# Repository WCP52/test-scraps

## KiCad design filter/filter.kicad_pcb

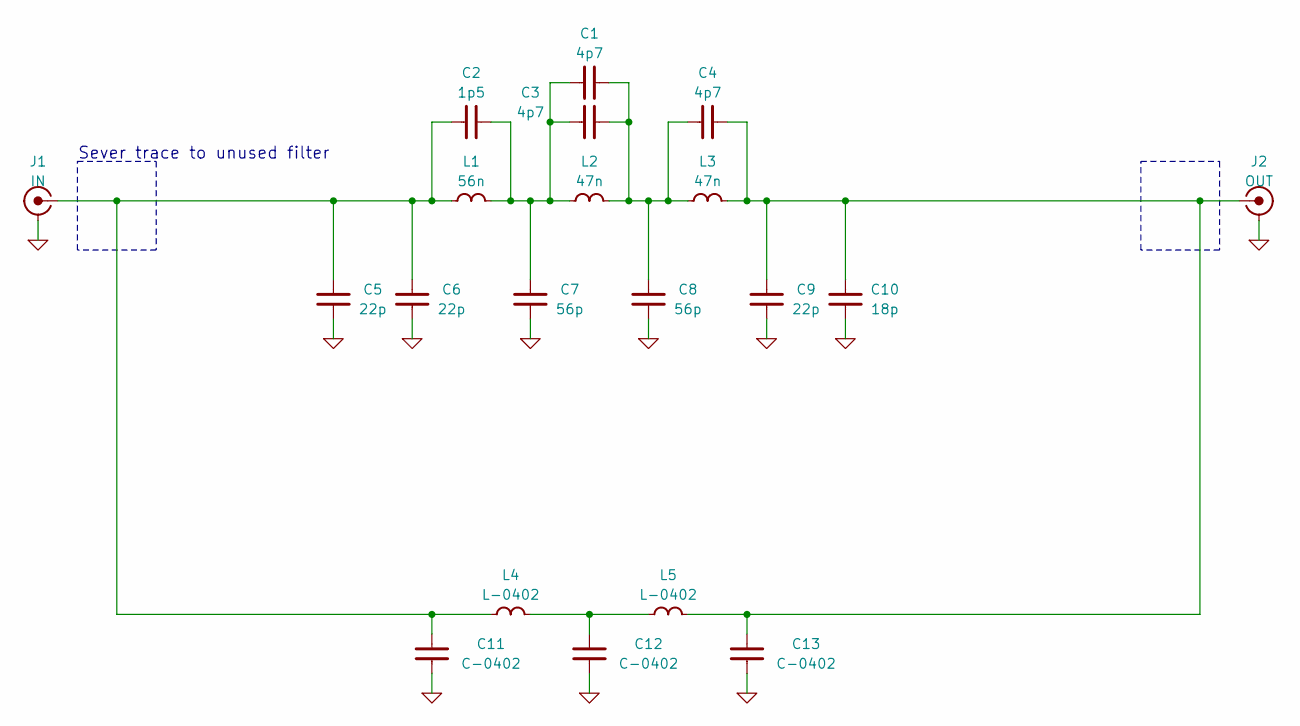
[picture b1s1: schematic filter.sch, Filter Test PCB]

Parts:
C1, C3, C4: 4p7; CAPC1005X55
C2: 1p5; CAPC1005X55
C5, C6, C9: 22p; CAPC1005X55
C7, C8: 56p; CAPC1005X55
C10: 18p; CAPC1005X55
C11, C12, C13: C-0402; CAPC1005X55
J1: IN; CONN-CONSMA001
J2: OUT; CONN-CONSMA001
L1: 56n; INDC1005X60
L2, L3: 47n; INDC1005X60
L4, L5: L-0402; INDC1005X60

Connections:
GND: C5.2, C6.2, C7.2, C8.2, C9.2, C10.2, C11.2, C12.2, C13.2, J1.2, J2.2
unnamed: C1.1, C3.1, C4.2, C8.1, L2.1, L3.2
unnamed: C1.2, C2.1, C3.2, C7.1, L1.1, L2.2
unnamed: C4.1, C9.1, C10.1, C13.1, J2.1, L3.1, L5.1
unnamed: C2.2, C5.1, C6.1, C11.1, J1.1, L1.2, L4.2
unnamed: C12.1, L4.1, L5.2

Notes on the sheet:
Sever trace to unused filter

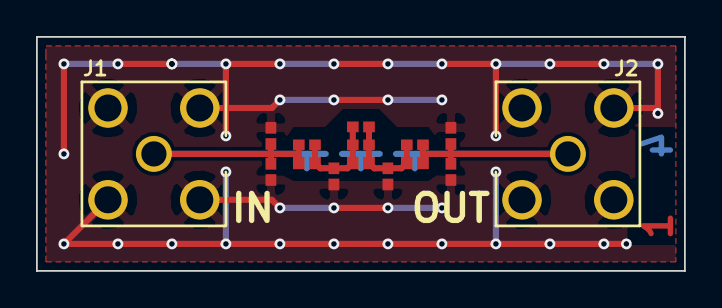
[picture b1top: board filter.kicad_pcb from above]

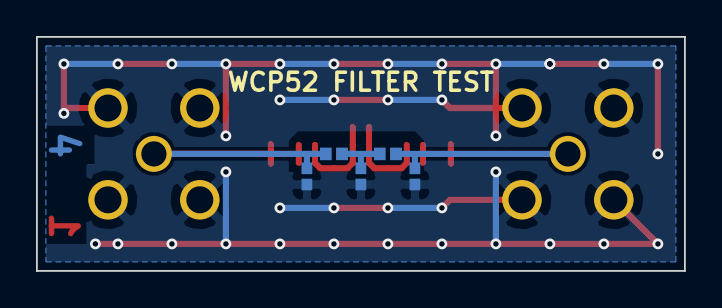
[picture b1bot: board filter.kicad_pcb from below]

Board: 4 copper layers, 36.0 x 13.0 mm, 20 parts (5 on the bottom side), 6 nets.

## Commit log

2015-02-22 Added filter board
2015-02-22 Prepared for ordering
